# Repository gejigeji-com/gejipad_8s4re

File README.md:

# gejipad_8s4re

自作キーボード「gejipad_8s4re」のハードウェア設計データ(KiCad)を公開するリポジトリです。

> **Note:** このリポジトリにはハードウェア(回路図・基板データ)のみを収録しています。ファームウェアはQMK Firmwareへの統合を申請中(`gejigeji/gejipad_8s4re`)であり、本リポジトリには含まれません。

## 概要

| 項目 | 内容 |
|---|---|
| キー数 | 8キー |
| ロータリーエンコーダ | 4基 |
| レイアウト | キー1列 + ロータリーエンコーダ1列 |
| MCU | ATmega32U4 |
| スイッチ | MX互換 |
| ファームウェア | [QMK Firmware](https://github.com/qmk/qmk_firmware) `gejigeji/gejipad_8s4re` として申請中(本リポジトリには含まれません) |

## リポジトリ構成

```
gejipad_8s4re/
├── gejipad_8s4re.kicad_pro   # KiCadプロジェクトファイル
├── gejipad_8s4re.kicad_sch   # 回路図
├── gejipad_8s4re.kicad_pcb   # 基板データ
├── libs/                     # 自作/追加ライブラリ(シンボル・フットプリント・3Dモデル)
├── production/                # 発注用データ(ガーバー・BOM・部品配置)・ケース
└── docs/                      # 回路図PDF・基板画像など
```

## 開発環境

- KiCad 7.0

## 基板の発注方法

`production/gerbers/` 内のガーバーデータをPCB製造業者(JLCPCBなど)にアップロード

## 組み立て

1. 部品は [`production/gejipad_8s4re-BOM.csv`](production/gejipad_8s4re-bom.csv) を参照
2. 組み立て方法は [`docs/assembly.md`](docs/assembly.md) を参照

## ファームウェアについて

本キーボードのファームウェアは [QMK Firmware](https://github.com/qmk/qmk_firmware) への統合を申請中です(統合先パス: `keyboards/gejigeji/gejipad_8s4re/`)。現時点では未マージのため、ハードウェア(本リポジトリ)とは別管理とし、キーマップ等のファームウェア関連ファイルはこのリポジトリには含めていません。

<!-- PRのURLが判明したら、ここに追記します -->

マージ後はQMK Firmwareの `keyboards/gejigeji/gejipad_8s4re/` に統合される予定です。

## ライセンス

本リポジトリのハードウェア設計データ(回路図・基板データ)は [CC BY-SA 4.0](https://creativecommons.org/licenses/by-sa/4.0/)(Creative Commons Attribution-ShareAlike 4.0 International)のもとで公開しています。改変・再配布・商用利用は自由ですが、クレジット表記(Attribution)と、改変版を同じライセンスで公開すること(ShareAlike)が条件となります。詳細は [LICENSE](./LICENSE) を参照してください。

ファームウェア部分は本リポジトリに含まれないため、このライセンスの対象外です。QMK Firmwareへの統合後は、QMK側のライセンス(GPLv2/v3)に従います。

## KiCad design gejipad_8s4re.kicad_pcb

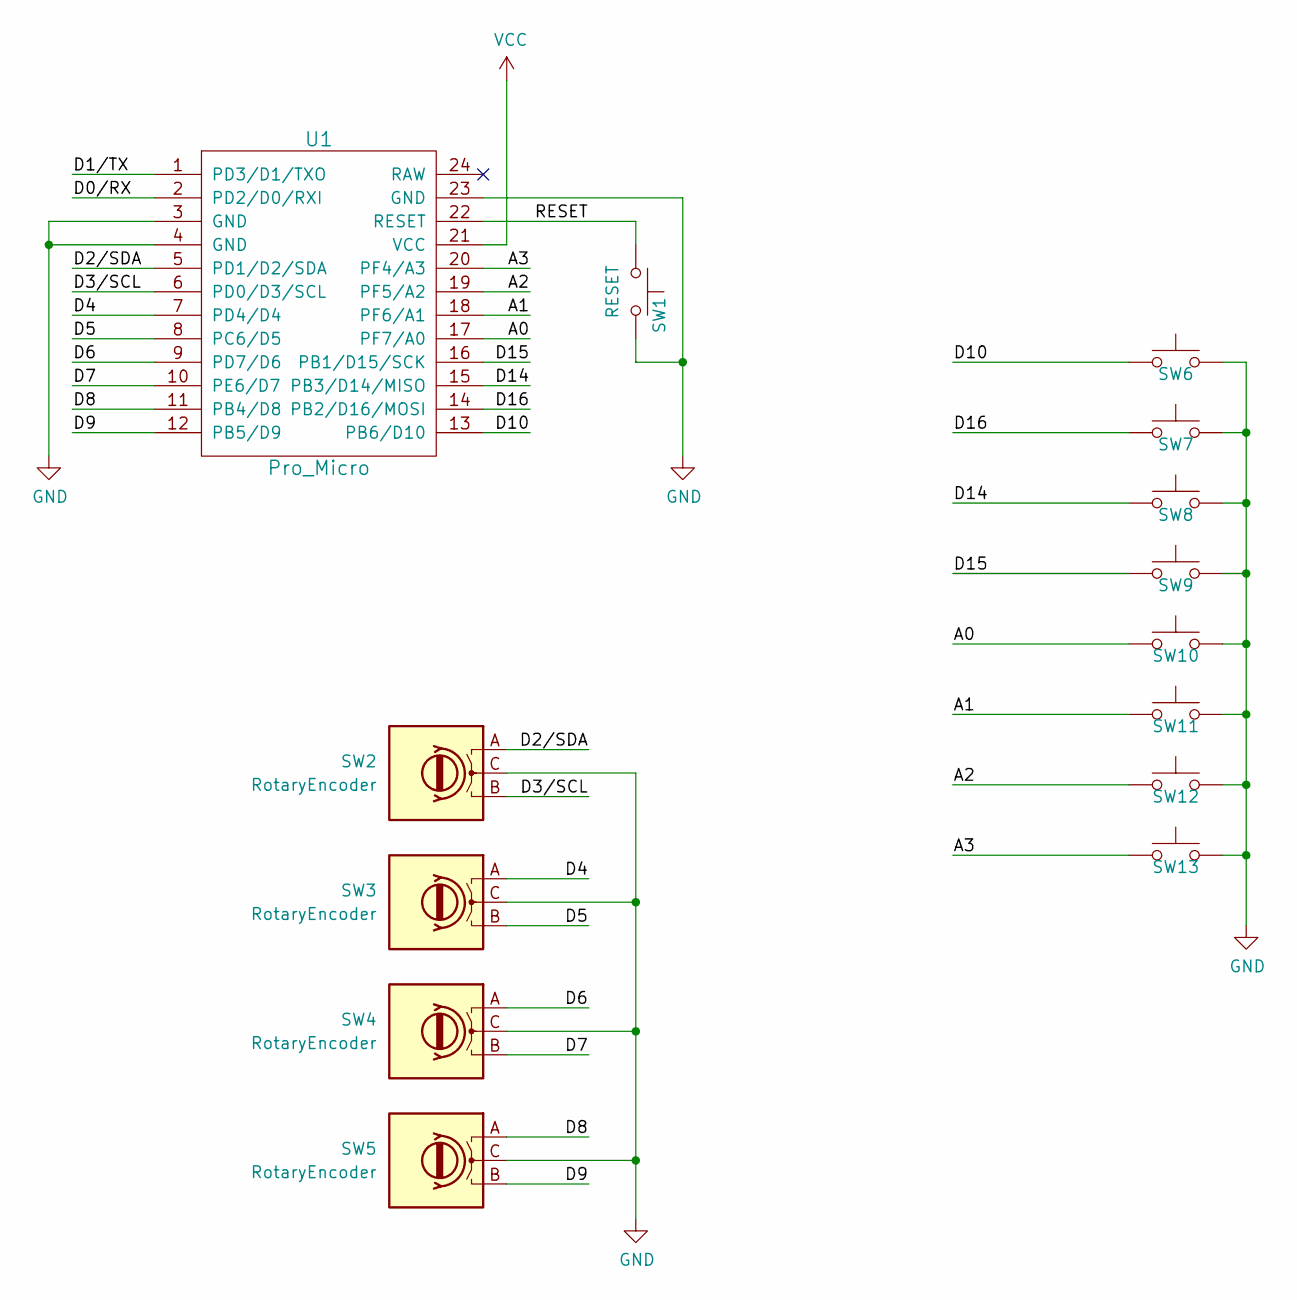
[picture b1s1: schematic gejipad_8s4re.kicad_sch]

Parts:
SW1: RESET; SW_PUSH_6mm
SW2, SW3, SW4, SW5: RotaryEncoder; RotaryEncoder_Alps_EC12E_Vertical_H20mm
SW6, SW7, SW8, SW9, SW10, SW11, SW12, SW13: SW_Push; SW_Cherry_MX1A_1.00u_PCB
U1: Pro_Micro; ProMicro

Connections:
/A0: SW10.1, U1.17 (PF7/A0)
/A1: SW11.1, U1.18 (PF6/A1)
/A2: SW12.1, U1.19 (PF5/A2)
/A3: SW13.1, U1.20 (PF4/A3)
/D0/RX: U1.2 (PD2/D0/RXI)
/D1/TX: U1.1 (PD3/D1/TXO)
/D2/SDA: SW2.A, U1.5 (PD1/D2/SDA)
/D3/SCL: SW2.B, U1.6 (PD0/D3/SCL)
/D4: SW3.A, U1.7 (PD4/D4)
/D5: SW3.B, U1.8 (PC6/D5)
/D6: SW4.A, U1.9 (PD7/D6)
/D7: SW4.B, U1.10 (PE6/D7)
/D8: SW5.A, U1.11 (PB4/D8)
/D9: SW5.B, U1.12 (PB5/D9)
/D10: SW6.1, U1.13 (PB6/D10)
/D14: SW8.1, U1.15 (PB3/D14/MISO)
/D15: SW9.1, U1.16 (PB1/D15/SCK)
/D16: SW7.1, U1.14 (PB2/D16/MOSI)
/RESET: SW1.1, U1.22 (RESET)
GND: SW1.2, SW2.C, SW3.C, SW4.C, SW5.C, SW6.2, SW7.2, SW8.2, SW9.2, SW10.2, SW11.2, SW12.2, SW13.2, U1.3 (GND), U1.4 (GND), U1.23 (GND)
VCC: U1.21 (VCC)

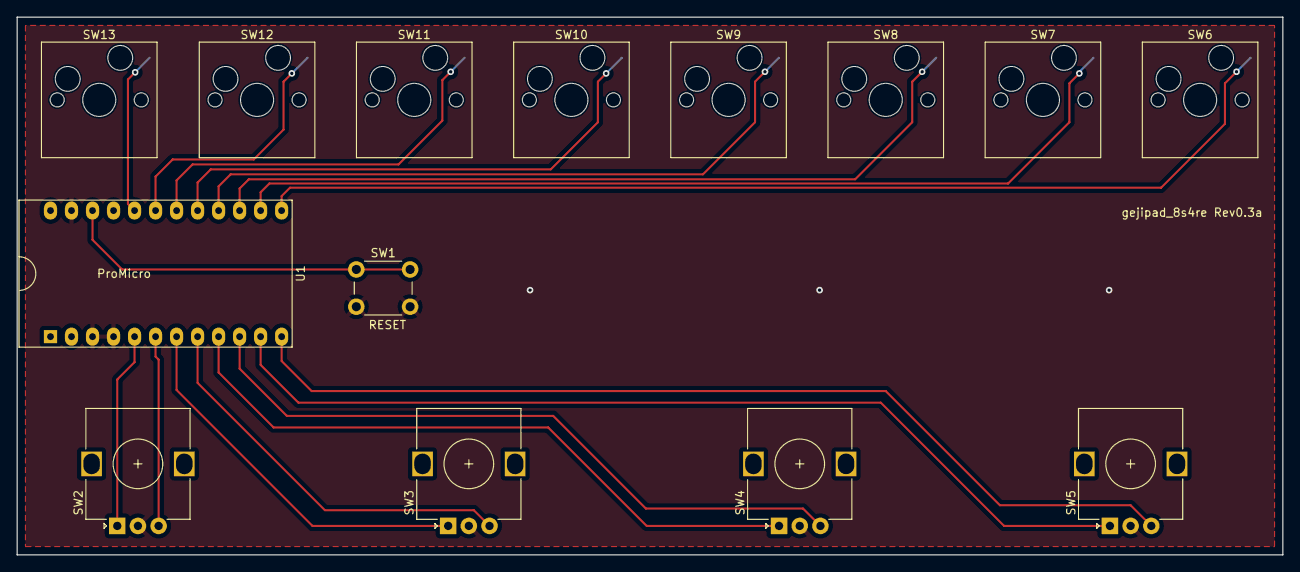
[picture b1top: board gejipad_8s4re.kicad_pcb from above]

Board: 2 copper layers, 153.0 x 65.0 mm, 14 parts (0 on the bottom side), 18 nets.
